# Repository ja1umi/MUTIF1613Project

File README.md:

# MUTIF1613Project
This project aims to build a vintage PANAFACOM's 16-bit MN1613-based computer. All the project-related files are available here.

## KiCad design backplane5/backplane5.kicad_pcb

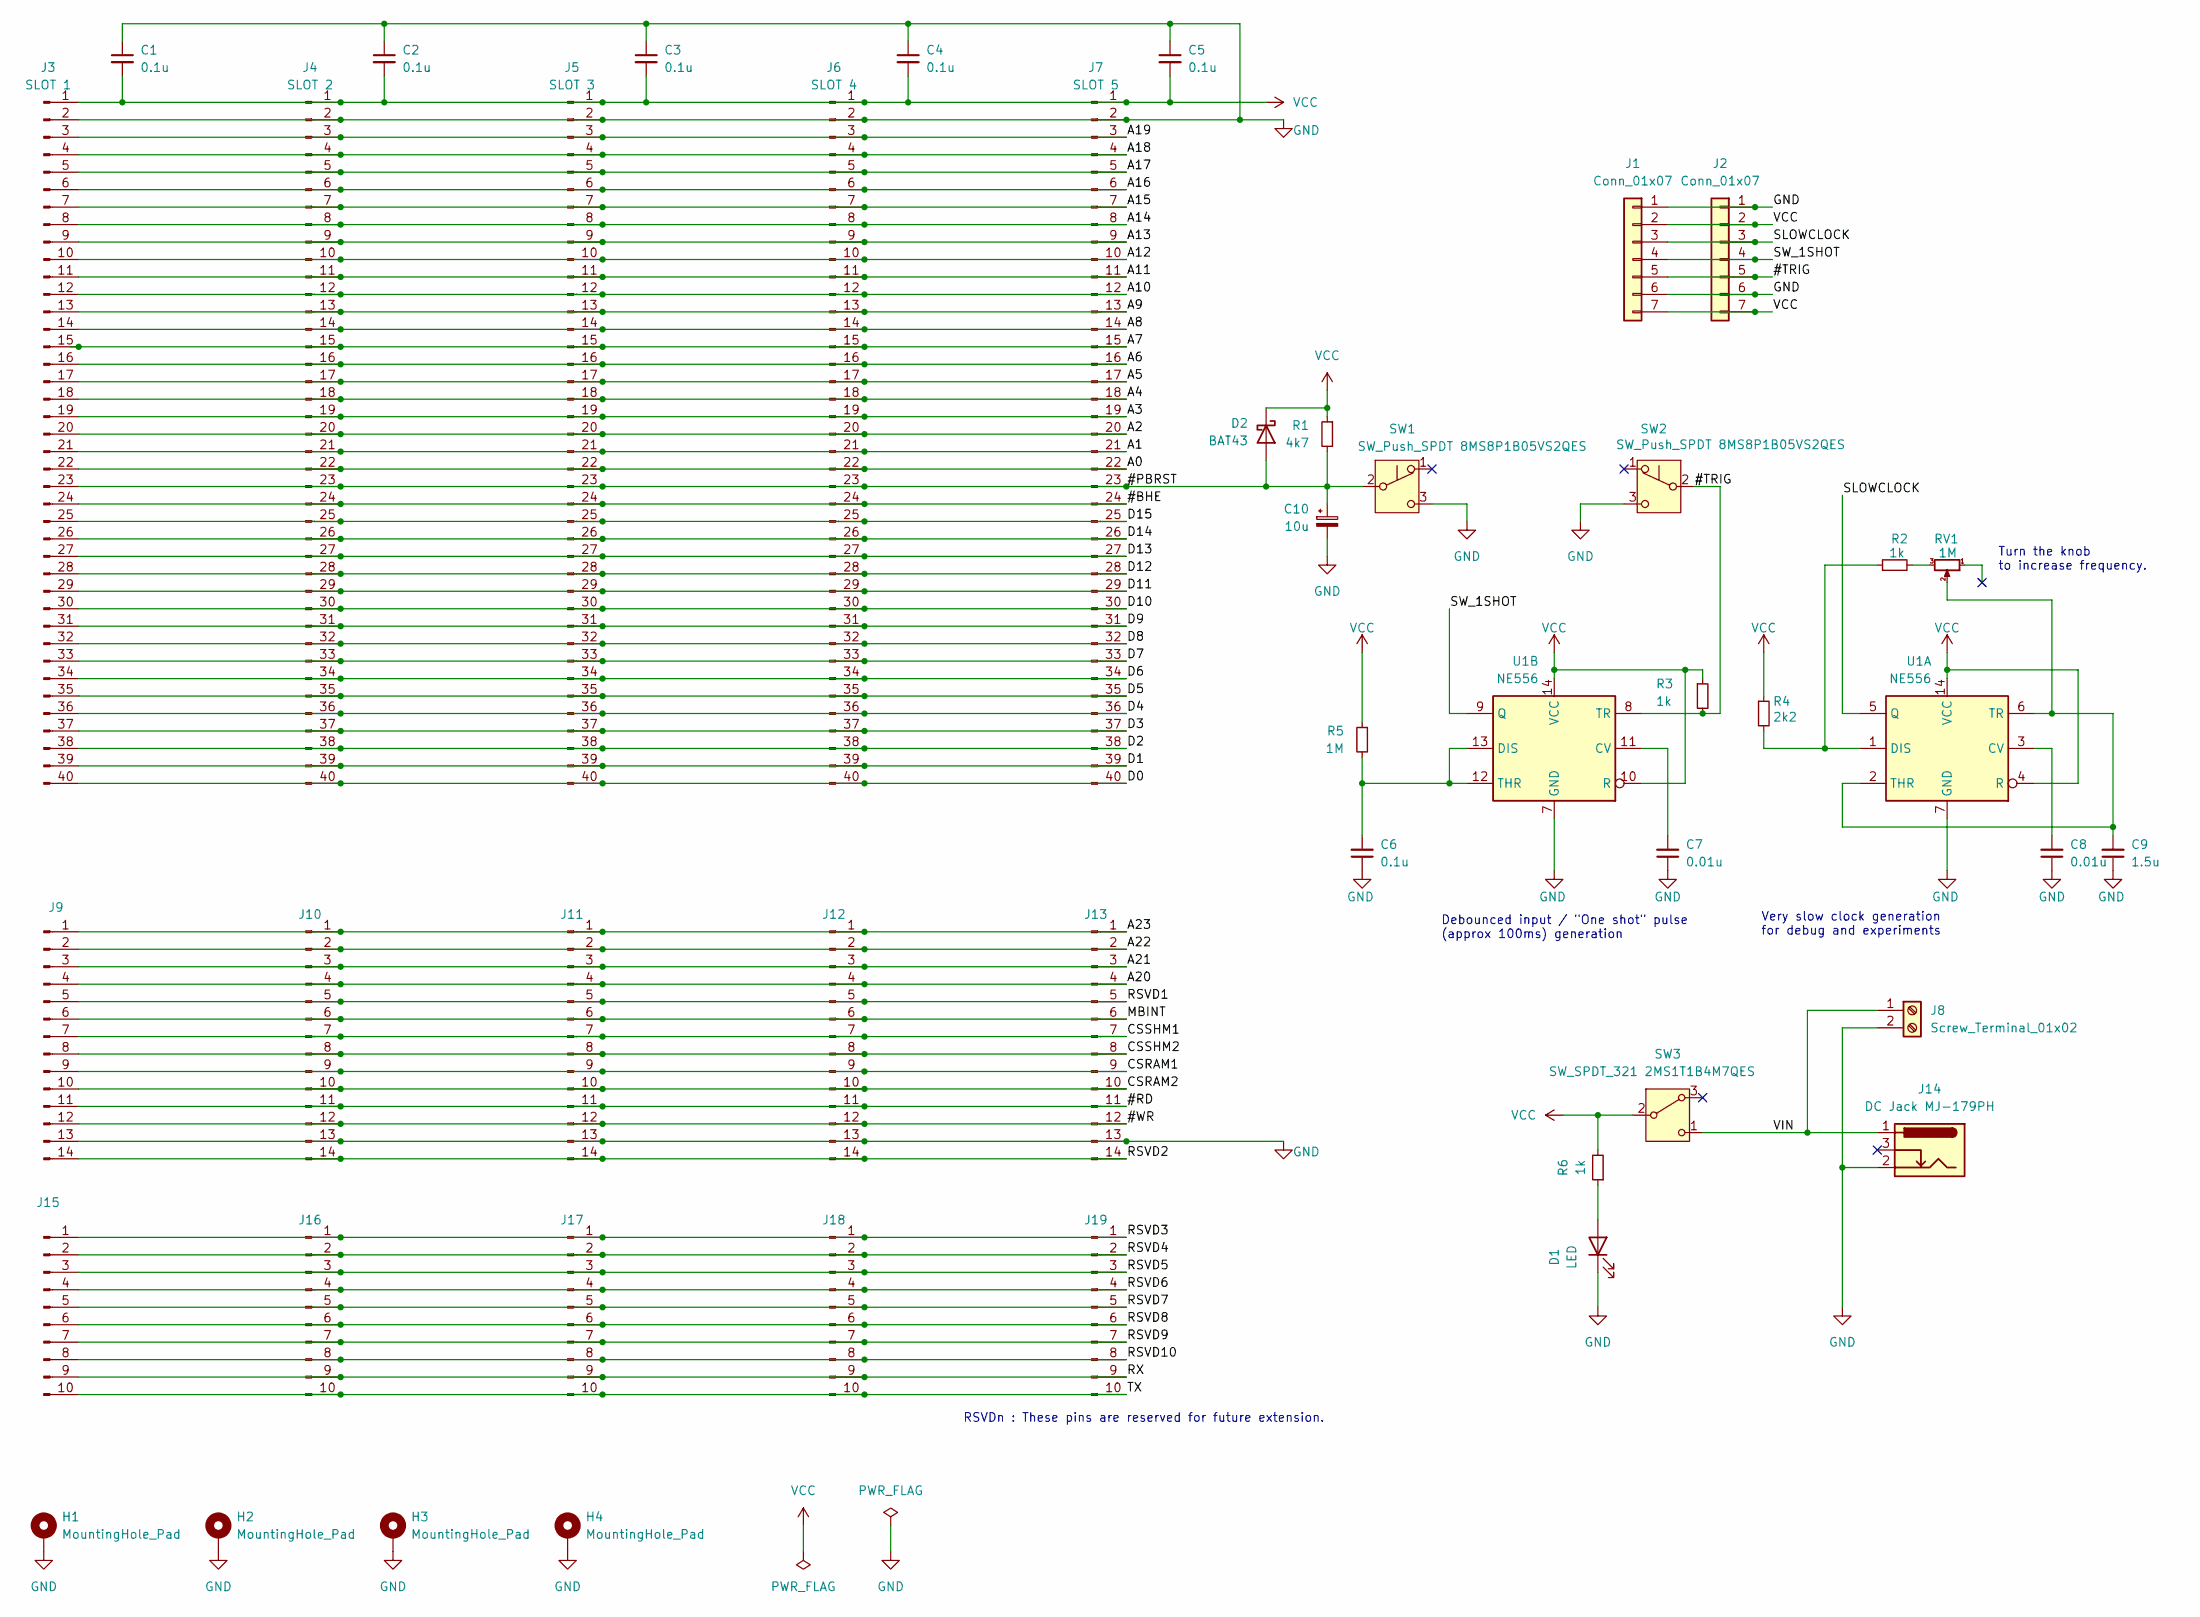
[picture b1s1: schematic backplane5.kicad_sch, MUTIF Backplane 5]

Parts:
C1, C2, C3, C4, C5, C6: 0.1u; C_Disc_D5.0mm_W2.5mm_P2.50mm
C7, C8: 0.01u; C_Disc_D5.0mm_W2.5mm_P2.50mm
C9: 1.5u; C_Disc_D5.0mm_W2.5mm_P5.00mm
C10: 10u; CP_Radial_D5.0mm_P2.50mm
D1: LED; LED_D5.0mm
D2: BAT43; D_DO-35_SOD27_P7.62mm_Horizontal
H1, H2, H3, H4: MountingHole_Pad; MountingHole_3.2mm_M3_Pad
J1, J2: Conn_01x07; PinHeader_1x07_P2.54mm_Vertical
J3: SLOT 1; PinHeader_1x40_P2.54mm_Vertical
J4: SLOT 2; PinHeader_1x40_P2.54mm_Vertical
J5: SLOT 3; PinHeader_1x40_P2.54mm_Vertical
J6: SLOT 4; PinHeader_1x40_P2.54mm_Vertical
J7: SLOT 5; PinHeader_1x40_P2.54mm_Vertical
J8: Screw_Terminal_01x02; TerminalBlock_Phoenix_MKDS-1,5-2-5.08_1x02_P5.08mm_Horizont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
J9, J10, J11, J12, J13: Conn_01x14_Pin; PinHeader_1x14_P2.54mm_Vertical
J14: DC Jack MJ-179PH; MJ-179PH
J15, J16, J17, J18, J19: Conn_01x10_Pin; PinHeader_1x10_P2.54mm_Vertical
R1: 4k7; R_Axial_DIN0204_L3.6mm_D1.6mm_P7.62mm_Horizontal
R2, R3, R6: 1k; R_Axial_DIN0204_L3.6mm_D1.6mm_P7.62mm_Horizontal
R4: 2k2; R_Axial_DIN0204_L3.6mm_D1.6mm_P7.62mm_Horizontal
R5: 1M; R_Axial_DIN0204_L3.6mm_D1.6mm_P7.62mm_Horizontal
RV1: 1M; Potentiometer_Bourns_3296W_Vertical
SW1, SW2: SW_Push_SPDT 8MS8P1B05VS2QES; 8MSP0340
SW3: SW_SPDT_321 2MS1T1B4M7QES; 2MS1T1B4M7QES
U1: NE556; DIP-14_W7.62mm_LongPads

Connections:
/#BHE: J3.24, J4.24, J5.24, J6.24, J7.24
/#PBRST: C10.1, D2.2 (A), J3.23, J4.23, J5.23, J6.23, J7.23, R1.2, SW1.2 (B)
/#RD: J9.11, J10.11, J11.11, J12.11, J13.11
/#TRIG: J1.5, J2.5, R3.2, SW2.2 (B), U1.8 (TR)
/#WR: J9.12, J10.12, J11.12, J12.12, J13.12
/A0: J3.22, J4.22, J5.22, J6.22, J7.22
/A1: J3.21, J4.21, J5.21, J6.21, J7.21
/A2: J3.20, J4.20, J5.20, J6.20, J7.20
/A3: J3.19, J4.19, J5.19, J6.19, J7.19
/A4: J3.18, J4.18, J5.18, J6.18, J7.18
/A5: J3.17, J4.17, J5.17, J6.17, J7.17
/A6: J3.16, J4.16, J5.16, J6.16, J7.16
/A7: J3.15, J4.15, J5.15, J6.15, J7.15
/A8: J3.14, J4.14, J5.14, J6.14, J7.14
/A9: J3.13, J4.13, J5.13, J6.13, J7.13
/A10: J3.12, J4.12, J5.12, J6.12, J7.12
/A11: J3.11, J4.11, J5.11, J6.11, J7.11
/A12: J3.10, J4.10, J5.10, J6.10, J7.10
/A13: J3.9, J4.9, J5.9, J6.9, J7.9
/A14: J3.8, J4.8, J5.8, J6.8, J7.8
/A15: J3.7, J4.7, J5.7, J6.7, J7.7
/A16: J3.6, J4.6, J5.6, J6.6, J7.6
/A17: J3.5, J4.5, J5.5, J6.5, J7.5
/A18: J3.4, J4.4, J5.4, J6.4, J7.4
/A19: J3.3, J4.3, J5.3, J6.3, J7.3
/A20: J9.4, J10.4, J11.4, J12.4, J13.4
/A21: J9.3, J10.3, J11.3, J12.3, J13.3
/A22: J9.2, J10.2, J11.2, J12.2, J13.2
/A23: J9.1, J10.1, J11.1, J12.1, J13.1
/CSRAM1: J9.9, J10.9, J11.9, J12.9, J13.9
/CSRAM2: J9.10, J10.10, J11.10, J12.10, J13.10
/CSSHM1: J9.7, J10.7, J11.7, J12.7, J13.7
/CSSHM2: J9.8, J10.8, J11.8, J12.8, J13.8
/D0: J3.40, J4.40, J5.40, J6.40, J7.40
/D1: J3.39, J4.39, J5.39, J6.39, J7.39
/D2: J3.38, J4.38, J5.38, J6.38, J7.38
/D3: J3.37, J4.37, J5.37, J6.37, J7.37
/D4: J3.36, J4.36, J5.36, J6.36, J7.36
/D5: J3.35, J4.35, J5.35, J6.35, J7.35
/D6: J3.34, J4.34, J5.34, J6.34, J7.34
/D7: J3.33, J4.33, J5.33, J6.33, J7.33
/D8: J3.32, J4.32, J5.32, J6.32, J7.32
/D9: J3.31, J4.31, J5.31, J6.31, J7.31
/D10: J3.30, J4.30, J5.30, J6.30, J7.30
/D11: J3.29, J4.29, J5.29, J6.29, J7.29
/D12: J3.28, J4.28, J5.28, J6.28, J7.28
/D13: J3.27, J4.27, J5.27, J6.27, J7.27
/D14: J3.26, J4.26, J5.26, J6.26, J7.26
/D15: J3.25, J4.25, J5.25, J6.25, J7.25
/MBINT: J9.6, J10.6, J11.6, J12.6, J13.6
/RSVD1: J9.5, J10.5, J11.5, J12.5, J13.5
/RSVD2: J9.14, J10.14, J11.14, J12.14, J13.14
/RSVD3: J15.1, J16.1, J17.1, J18.1, J19.1
/RSVD4: J15.2, J16.2, J17.2, J18.2, J19.2
/RSVD5: J15.3, J16.3, J17.3, J18.3, J19.3
/RSVD6: J15.4, J16.4, J17.4, J18.4, J19.4
/RSVD7: J15.5, J16.5, J17.5, J18.5, J19.5
/RSVD8: J15.6, J16.6, J17.6, J18.6, J19.6
/RSVD9: J15.7, J16.7, J17.7, J18.7, J19.7
/RSVD10: J15.8, J16.8, J17.8, J18.8, J19.8
/RX: J15.9, J16.9, J17.9, J18.9, J19.9
/SLOWCLOCK: J1.3, J2.3, U1.5 (Q)
/SW_1SHOT: J1.4, J2.4, U1.9 (Q)
/TX: J15.10, J16.10, J17.10, J18.10, J19.10
/VIN: J8.1, J14.1, SW3.1 (C)
GND: C1.1, C2.1, C3.1, C4.1, C5.1, C6.1, C7.1, C8.1, C9.1, C10.2, D1.1 (K), H1.1, H2.1, H3.1, H4.1, J1.1, J1.6, J2.1, J2.6, J3.2, J4.2, J5.2, J6.2, J7.2, J8.2, J9.13, J10.13, J11.13, J12.13, J13.13, J14.2, SW1.3 (C), SW2.3 (C), U1.7 (GND)
unnamed: D1.2 (A), R6.1
unnamed: R2.2, RV1.3
unnamed: C8.2, U1.3 (CV)
unnamed: R2.1, R4.2, U1.1 (DIS)
unnamed: C9.2, RV1.2, U1.2 (THR), U1.6 (TR)
unnamed: C7.2, U1.11 (CV)
unnamed: C6.2, R5.2, U1.12 (THR), U1.13 (DIS)
VCC: C1.2, C2.2, C3.2, C4.2, C5.2, D2.1 (K), J1.2, J1.7, J2.2, J2.7, J3.1, J4.1, J5.1, J6.1, J7.1, R1.1, R3.1, R4.1, R5.1, R6.2, SW3.2 (B), U1.4 (R), U1.10 (R), U1.14 (VCC)

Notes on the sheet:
RSVDn : These pins are reserved for future extension.
Turn the knob to increase frequency.
Very slow clock generation for debug and experiments
Debounced input / "One shot" pulse (approx 100ms) generation

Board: 2 copper layers, 46 parts (0 on the bottom side), 74 nets, no tracks yet.

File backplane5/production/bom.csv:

Designator,Footprint,Quantity,Value,LCSC Part #
"C1, C2, C3, C4, C5, C6",C_Disc_D5.0mm_W2.5mm_P2.50mm,6,0.1u,
"C7, C8",C_Disc_D5.0mm_W2.5mm_P2.50mm,2,0.01u,
C9,C_Disc_D5.0mm_W2.5mm_P5.00mm,1,1.5u,
D1,LED_D5.0mm,1,LED,
"J1, J2",PinHeader_1x06_P2.54mm_Vertical,2,Conn_01x06,
"J10, J11, J12, J13, J9",PinHeader_1x14_P2.54mm_Vertical,5,Conn_01x14_Pin,
J14,MJ-179PH,1,DC Jack MJ-179PH,
"J15, J16, J17, J18, J19",PinHeader_1x10_P2.54mm_Vertical,5,Conn_01x10_Pin,
J3,PinHeader_1x40_P2.54mm_Vertical,1,SLOT 1,
J4,PinHeader_1x40_P2.54mm_Vertical,1,SLOT 2,
J5,PinHeader_1x40_P2.54mm_Vertical,1,SLOT 3,
J6,PinHeader_1x40_P2.54mm_Vertical,1,SLOT 4,
J7,PinHeader_1x40_P2.54mm_Vertical,1,SLOT 5,
J8,"TerminalBlock_Phoenix_MKDS-1,5-2-5.08_1x02_P5.08mm_Horizontal",1,Screw_Terminal_01x02,
R1,R_Axial_DIN0204_L3.6mm_D1.6mm_P7.62mm_Horizontal,1,4k7,
"R2, R3, R6",R_Axial_DIN0204_L3.6mm_D1.6mm_P7.62mm_Horizontal,3,1k,
R4,R_Axial_DIN0204_L3.6mm_D1.6mm_P7.62mm_Horizontal,1,2k2,
R5,R_Axial_DIN0204_L3.6mm_D1.6mm_P7.62mm_Horizontal,1,1M,
RV1,Potentiometer_Bourns_3296W_Vertical,1,1M,
"SW1, SW2",8MSP0340,2,SW_Push_SPDT 8MS8P1B05VS2QES,
SW3,2MS1T1B4M7QES,1,SW_SPDT_321 2MS1T1B4M7QES,
U1,DIP-14_W7.62mm_LongPads,1,NE556,

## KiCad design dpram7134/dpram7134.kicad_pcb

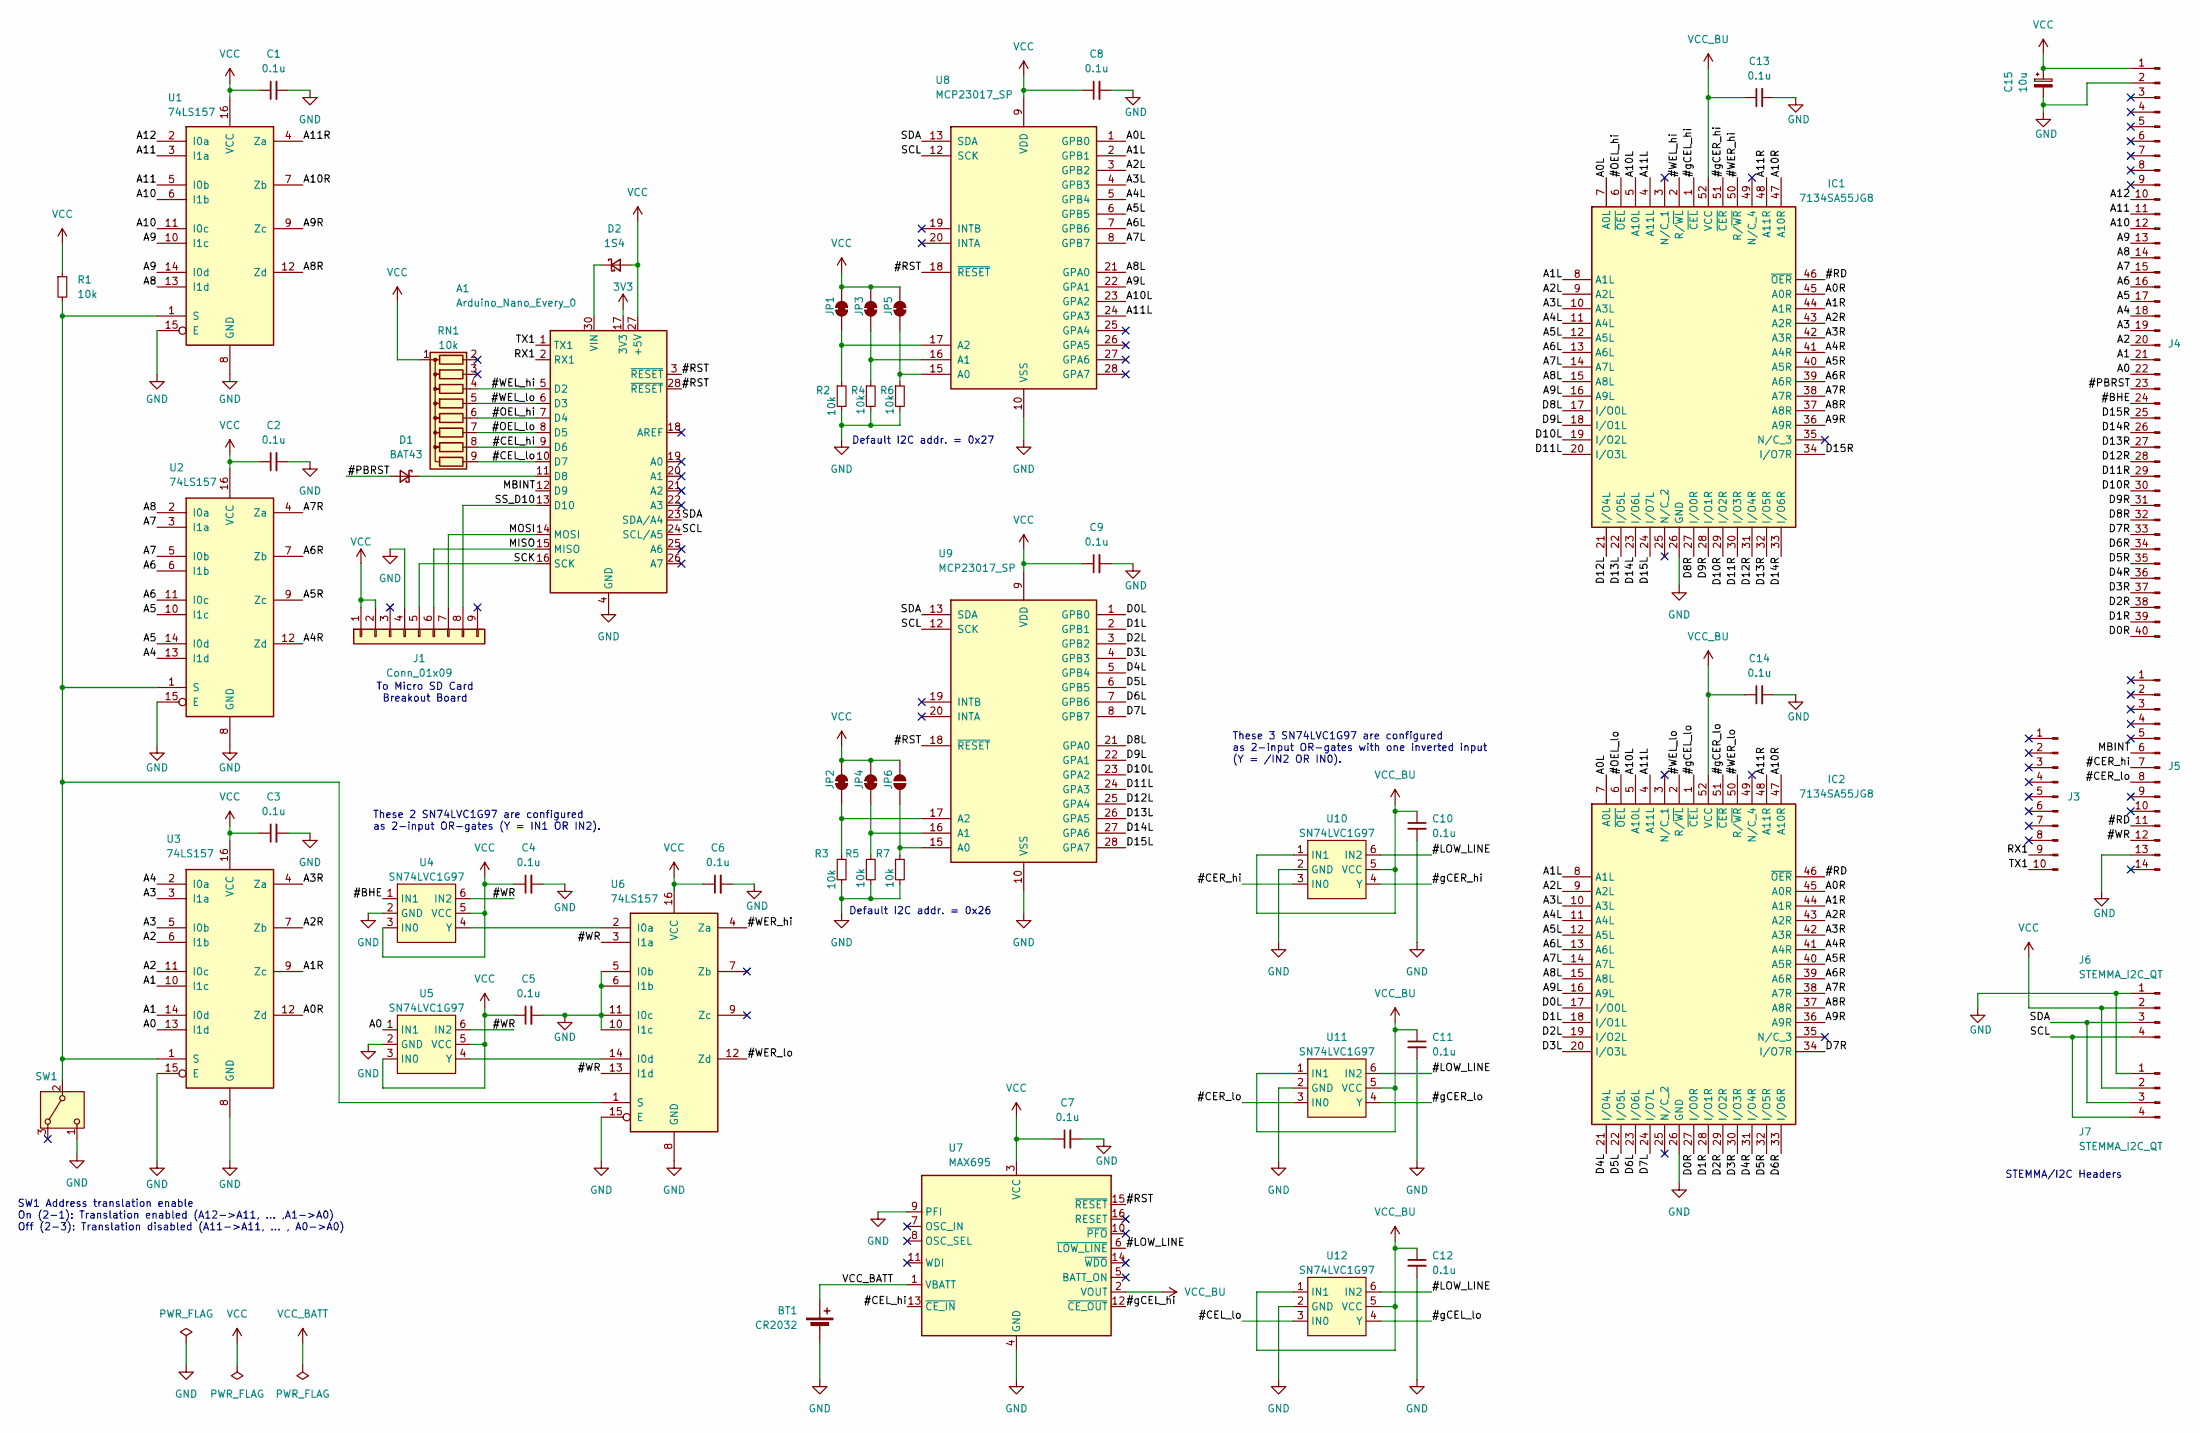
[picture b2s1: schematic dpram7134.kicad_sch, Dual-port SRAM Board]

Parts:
A1: Arduino_Nano_Every_0; Arduino_Nano
BT1: CR2032; CH243-2032LF
C1, C2, C3, C4, C5, C6, C7, C8, C9, C10, C11, C12, C13, C14: 0.1u; C_Disc_D5.0mm_W2.5mm_P5.00mm
C15: 10u; CP_Radial_D5.0mm_P2.50mm
D1: BAT43; D_DO-35_SOD27_P7.62mm_Horizontal
D2: 1S4; D_DO-35_SOD27_P7.62mm_Horizontal
IC1, IC2: 7134SA55JG8; PLCC-52_THT-Socket; Mouser Part Number 972-7134SA55JG8
J1: Conn_01x09; PinHeader_1x09_P2.54mm_Vertical
J3: Conn_01x10_Pin; PinHeader_1x10_P2.54mm_Vertical
J4: Conn_01x40_Pin; PinHeader_1x40_P2.54mm_Vertical
J5: Conn_01x14_Pin; PinHeader_1x14_P2.54mm_Vertical
J6, J7: STEMMA_I2C_QT; JST_SH_SM04B-SRSS-TB_1x04-1MP_P1.00mm_Horizontal
JP1, JP2, JP3, JP4, JP5: SolderJumper_2_Bridged; SolderJumper-2_P1.3mm_Open_Pad1.0x1.5mm
JP6: SolderJumper_2_Open; SolderJumper-2_P1.3mm_Open_Pad1.0x1.5mm
R1, R2, R3, R4, R5, R6, R7: 10k; R_Axial_DIN0207_L6.3mm_D2.5mm_P7.62mm_Horizontal
RN1: 10k; R_Array_SIP9
SW1: SW_SPDT_321; PinHeader_1x03_P2.54mm_Vertical
U1, U2, U3, U6: 74LS157; DIP-16_W7.62mm_LongPads
U4, U5, U10, U11, U12: SN74LVC1G97; SOT-23-6
U7: MAX695; DIP-16_W7.62mm_LongPads
U8, U9: MCP23017_SP; DIP-28_W7.62mm_LongPads

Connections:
3V3: A1.17 (3V3)
/#BHE: J4.24, U4.1 (IN1)
/#CEL_hi: A1.9 (D6), RN1.8 (R7), U7.13 (~CE_IN)
/#CEL_lo: A1.10 (D7), RN1.9 (R8), U12.3 (IN0)
/#CER_hi: J5.7, U10.3 (IN0)
/#CER_lo: J5.8, U11.3 (IN0)
/#LOW_LINE: U7.6 (~LOW_LINE), U10.6 (IN2), U11.6 (IN2), U12.6 (IN2)
/#OEL_hi: A1.7 (D4), IC1.6 (~OEL), RN1.6 (R5)
/#OEL_lo: A1.8 (D5), IC2.6 (~OEL), RN1.7 (R6)
/#PBRST: D1.2 (A), J4.23
/#RD: IC1.46 (~OER), IC2.46 (~OER), J5.11
/#RST: A1.3 (~RESET), A1.28 (~RESET), U7.15 (~RESET), U8.18 (~RESET), U9.18 (~RESET)
/#WEL_hi: A1.5 (D2), IC1.2 (R/~WL), RN1.4 (R3)
/#WEL_lo: A1.6 (D3), IC2.2 (R/~WL), RN1.5 (R4)
/#WER_hi: IC1.50 (R/~WR), U6.4 (Za)
/#WER_lo: IC2.50 (R/~WR), U6.12 (Zd)
/#WR: J5.12, U4.6 (IN2), U5.6 (IN2), U6.3 (I1a), U6.13 (I1d)
/#gCEL_hi: IC1.1 (~CEL), U7.12 (~CE_OUT)
/#gCEL_lo: IC2.1 (~CEL), U12.4 (Y)
/#gCER_hi: IC1.51 (~CER), U10.4 (Y)
/#gCER_lo: IC2.51 (~CER), U11.4 (Y)
/A0: J4.22, U3.13 (I1d), U5.1 (IN1)
/A0L: IC1.7 (A0L), IC2.7 (A0L), U8.1 (GPB0)
/A0R: IC1.45 (A0R), IC2.45 (A0R), U3.12 (Zd)
/A1: J4.21, U3.10 (I1c), U3.14 (I0d)
/A1L: IC1.8 (A1L), IC2.8 (A1L), U8.2 (GPB1)
/A1R: IC1.44 (A1R), IC2.44 (A1R), U3.9 (Zc)
/A2: J4.20, U3.6 (I1b), U3.11 (I0c)
/A2L: IC1.9 (A2L), IC2.9 (A2L), U8.3 (GPB2)
/A2R: IC1.43 (A2R), IC2.43 (A2R), U3.7 (Zb)
/A3: J4.19, U3.3 (I1a), U3.5 (I0b)
/A3L: IC1.10 (A3L), IC2.10 (A3L), U8.4 (GPB3)
/A3R: IC1.42 (A3R), IC2.42 (A3R), U3.4 (Za)
/A4: J4.18, U2.13 (I1d), U3.2 (I0a)
/A4L: IC1.11 (A4L), IC2.11 (A4L), U8.5 (GPB4)
/A4R: IC1.41 (A4R), IC2.41 (A4R), U2.12 (Zd)
/A5: J4.17, U2.10 (I1c), U2.14 (I0d)
/A5L: IC1.12 (A5L), IC2.12 (A5L), U8.6 (GPB5)
/A5R: IC1.40 (A5R), IC2.40 (A5R), U2.9 (Zc)
/A6: J4.16, U2.6 (I1b), U2.11 (I0c)
/A6L: IC1.13 (A6L), IC2.13 (A6L), U8.7 (GPB6)
/A6R: IC1.39 (A6R), IC2.39 (A6R), U2.7 (Zb)
/A7: J4.15, U2.3 (I1a), U2.5 (I0b)
/A7L: IC1.14 (A7L), IC2.14 (A7L), U8.8 (GPB7)
/A7R: IC1.38 (A7R), IC2.38 (A7R), U2.4 (Za)
/A8: J4.14, U1.13 (I1d), U2.2 (I0a)
/A8L: IC1.15 (A8L), IC2.15 (A8L), U8.21 (GPA0)
/A8R: IC1.37 (A8R), IC2.37 (A8R), U1.12 (Zd)
/A9: J4.13, U1.10 (I1c), U1.14 (I0d)
/A9L: IC1.16 (A9L), IC2.16 (A9L), U8.22 (GPA1)
/A9R: IC1.36 (A9R), IC2.36 (A9R), U1.9 (Zc)
/A10: J4.12, U1.6 (I1b), U1.11 (I0c)
/A10L: IC1.5 (A10L), IC2.5 (A10L), U8.23 (GPA2)
/A10R: IC1.47 (A10R), IC2.47 (A10R), U1.7 (Zb)
/A11: J4.11, U1.3 (I1a), U1.5 (I0b)
/A11L: IC1.4 (A11L), IC2.4 (A11L), U8.24 (GPA3)
/A11R: IC1.48 (A11R), IC2.48 (A11R), U1.4 (Za)
/A12: J4.10, U1.2 (I0a)
/D0L: IC2.17 (I/O0L), U9.1 (GPB0)
/D0R: IC2.27 (I/O0R), J4.40
/D1L: IC2.18 (I/O1L), U9.2 (GPB1)
/D1R: IC2.28 (I/O1R), J4.39
/D2L: IC2.19 (I/O2L), U9.3 (GPB2)
/D2R: IC2.29 (I/O2R), J4.38
/D3L: IC2.20 (I/O3L), U9.4 (GPB3)
/D3R: IC2.30 (I/O3R), J4.37
/D4L: IC2.21 (I/O4L), U9.5 (GPB4)
/D4R: IC2.31 (I/O4R), J4.36
/D5L: IC2.22 (I/O5L), U9.6 (GPB5)
/D5R: IC2.32 (I/O5R), J4.35
/D6L: IC2.23 (I/O6L), U9.7 (GPB6)
/D6R: IC2.33 (I/O6R), J4.34
/D7L: IC2.24 (I/O7L), U9.8 (GPB7)
/D7R: IC2.34 (I/O7R), J4.33
/D8L: IC1.17 (I/O0L), U9.21 (GPA0)
/D8R: IC1.27 (I/O0R), J4.32
/D9L: IC1.18 (I/O1L), U9.22 (GPA1)
/D9R: IC1.28 (I/O1R), J4.31
/D10L: IC1.19 (I/O2L), U9.23 (GPA2)
/D10R: IC1.29 (I/O2R), J4.30
/D11L: IC1.20 (I/O3L), U9.24 (GPA3)
/D11R: IC1.30 (I/O3R), J4.29
/D12L: IC1.21 (I/O4L), U9.25 (GPA4)
/D12R: IC1.31 (I/O4R), J4.28
/D13L: IC1.22 (I/O5L), U9.26 (GPA5)
/D13R: IC1.32 (I/O5R), J4.27
/D14L: IC1.23 (I/O6L), U9.27 (GPA6)
/D14R: IC1.33 (I/O6R), J4.26
/D15L: IC1.24 (I/O7L), U9.28 (GPA7)
/D15R: IC1.34 (I/O7R), J4.25
/MBINT: A1.12 (D9), J5.6
/MISO: A1.15 (MISO), J1.6
/MOSI: A1.14 (MOSI), J1.7
/RX1: A1.2 (RX1), J3.9
/SCK: A1.16 (SCK), J1.5
/SCL: A1.24 (SCL/A5), J6.4, J7.4, U8.12 (SCK), U9.12 (SCK)
/SDA: A1.23 (SDA/A4), J6.3, J7.3, U8.13 (SDA), U9.13 (SDA)
/SS_D10: A1.13 (D10), J1.8
/TX1: A1.1 (TX1), J3.10
GND: A1.4 (GND), A1.29 (GND), BT1.2 (-), C1.2, C2.2, C3.2, C4.2, C5.2, C6.2, C7.2, C8.2, C9.2, C10.2, C11.2, C12.2, C13.2, C14.2, C15.2, IC1.26 (GND), IC2.26 (GND), J1.4, J4.2, J5.13, J6.1, J6.MP, J7.1, J7.MP, R2.2, R3.2, R4.2, R5.2, R6.2, R7.2, SW1.1 (C), U1.8 (GND), U1.15 (E), U2.8 (GND), U2.15 (E), U3.8 (GND), U3.15 (E), U4.2 (GND), U5.2 (GND), U6.5 (I0b), U6.6 (I1b), U6.8 (GND), U6.10 (I1c), U6.11 (I0c), U6.15 (E), U7.4 (GND), U7.9 (PFI), U8.10 (VSS), U9.10 (VSS), U10.2 (GND), U11.2 (GND), U12.2 (GND)
unnamed: A1.11 (D8), D1.1 (K)
unnamed: A1.30 (VIN), D2.1 (K)
unnamed: JP1.1 (A), R2.1, U8.17 (A2)
unnamed: JP2.1 (A), R3.1, U9.17 (A2)
unnamed: JP3.1 (A), R4.1, U8.16 (A1)
unnamed: JP4.1 (A), R5.1, U9.16 (A1)
unnamed: JP5.1 (A), R6.1, U8.15 (A0)
unnamed: JP6.1 (A), R7.1, U9.15 (A0)
unnamed: R1.2, SW1.2 (B), U1.1 (S), U2.1 (S), U3.1 (S), U6.1 (S)
unnamed: U4.4 (Y), U6.2 (I0a)
unnamed: U5.4 (Y), U6.14 (I0d)
VCC: A1.27 (+5V), C1.1, C2.1, C3.1, C4.1, C5.1, C6.1, C7.1, C8.1, C9.1, C15.1, D2.2 (A), J1.1, J1.2, J4.1, J6.2, J7.2, JP1.2 (B), JP2.2 (B), JP3.2 (B), JP4.2 (B), JP5.2 (B), JP6.2 (B), R1.1, RN1.1 (common), U1.16 (VCC), U2.16 (VCC), U3.16 (VCC), U4.3 (IN0), U4.5 (VCC), U5.3 (IN0), U5.5 (VCC), U6.16 (VCC), U7.3 (VCC), U8.9 (VDD), U9.9 (VDD)
VCC_BATT: BT1.1 (+), U7.1 (VBATT)
VCC_BU: C10.1, C11.1, C12.1, C13.1, C14.1, IC1.52 (VCC), IC2.52 (VCC), U7.2 (VOUT), U10.1 (IN1), U10.5 (VCC), U11.1 (IN1), U11.5 (VCC), U12.1 (IN1), U12.5 (VCC)

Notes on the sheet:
Default I2C addr. = 0x26
These 3 SN74LVC1G97 are configured as 2-input OR-gates with one inverted input (Y = /IN2 OR IN0).
Default I2C addr. = 0x27
To Micro SD Card Breakout Board
SW1 Address translation enable On (2-1): Translation enabled (A12->A11, ... ,A1->A0) Off (2-3): Translation disabled (A11->A11, ... , A0->A0)
These 2 SN74LVC1G97 are configured as 2-input OR-gates (Y = IN1 OR IN2).
STEMMA/I2C Headers

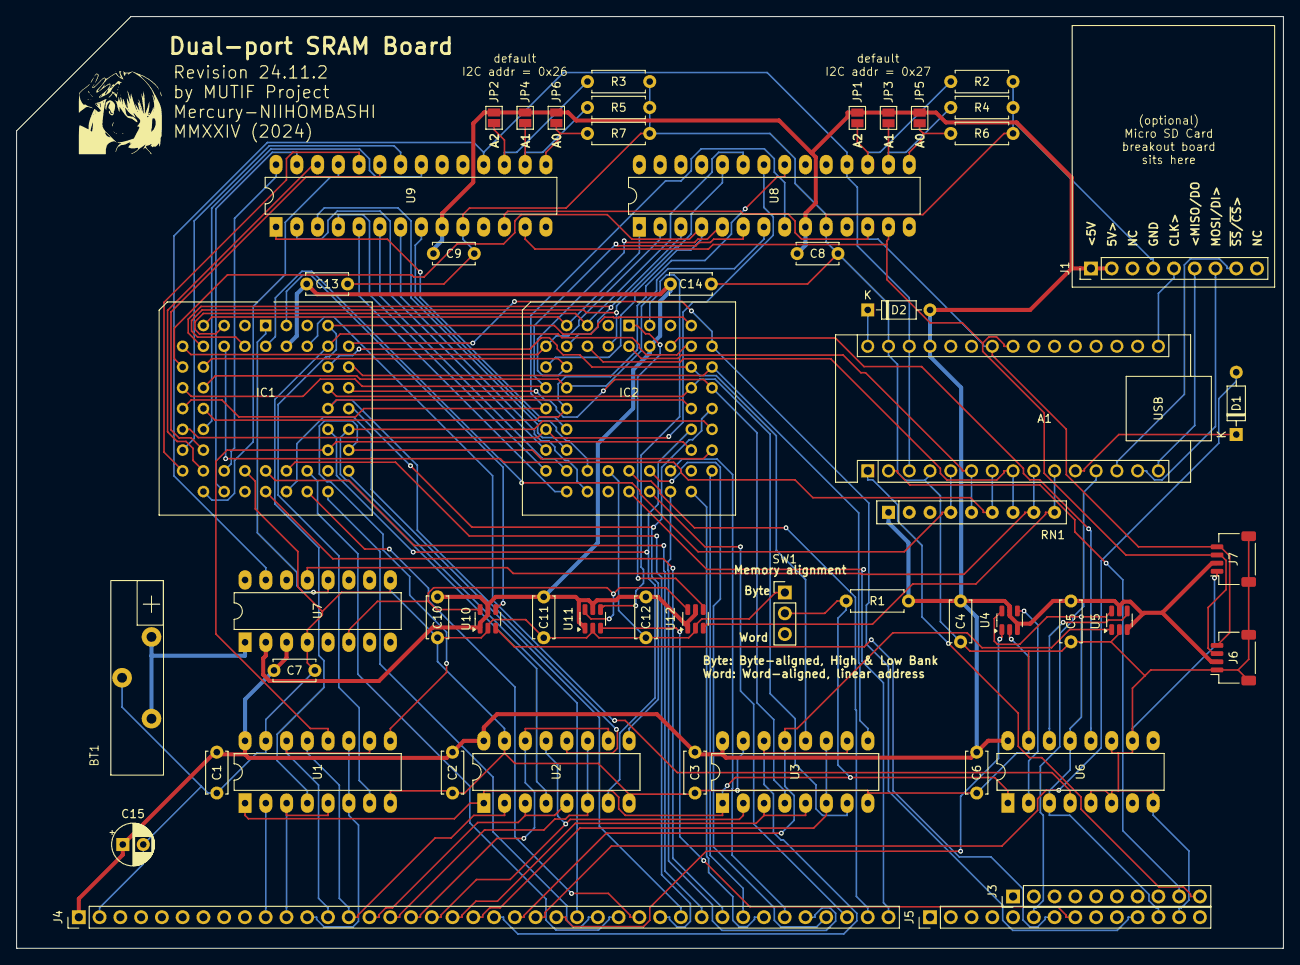
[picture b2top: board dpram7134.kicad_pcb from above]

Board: 2 copper layers, 155.0 x 114.0 mm, 54 parts (0 on the bottom side), 113 nets.

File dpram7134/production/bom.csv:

Designator,Footprint,Quantity,Value,LCSC Part #
A1,Arduino_Nano,1,Arduino_Nano_Every_0,
BT1,CH243-2032LF,1,CR2032,
"C1, C10, C11, C12, C13, C14, C2, C3, C4, C5, C6, C7, C8, C9",C_Disc_D5.0mm_W2.5mm_P5.00mm,14,0.1u,
C15,CP_Radial_D5.0mm_P2.50mm,1,10u,
D1,D_DO-35_SOD27_P7.62mm_Horizontal,1,BAT43,
D2,D_DO-35_SOD27_P7.62mm_Horizontal,1,1S4,
"IC1, IC2",PLCC-52_THT-Socket,2,7134SA55JG8,
J1,PinHeader_1x09_P2.54mm_Vertical,1,Conn_01x09,
J3,PinHeader_1x10_P2.54mm_Vertical,1,Conn_01x10_Pin,
J4,PinHeader_1x40_P2.54mm_Vertical,1,Conn_01x40_Pin,
J5,PinHeader_1x14_P2.54mm_Vertical,1,Conn_01x14_Pin,
"J6, J7",JST_SH_SM04B-SRSS-TB_1x04-1MP_P1.00mm_Horizontal,2,STEMMA_I2C_QT,
"R1, R2, R3, R4, R5, R6, R7",R_Axial_DIN0207_L6.3mm_D2.5mm_P7.62mm_Horizontal,7,10k,
RN1,R_Array_SIP9,1,10k,
SW1,PinHeader_1x03_P2.54mm_Vertical,1,SW_SPDT_321,
"U1, U2, U3, U6",DIP-16_W7.62mm_LongPads,4,74LS157,
"U10, U11, U12, U4, U5",SOT-23-6,5,SN74LVC1G97,
U7,DIP-16_W7.62mm_LongPads,1,MAX695,
"U8, U9",DIP-28_W7.62mm_LongPads,2,MCP23017_SP,
